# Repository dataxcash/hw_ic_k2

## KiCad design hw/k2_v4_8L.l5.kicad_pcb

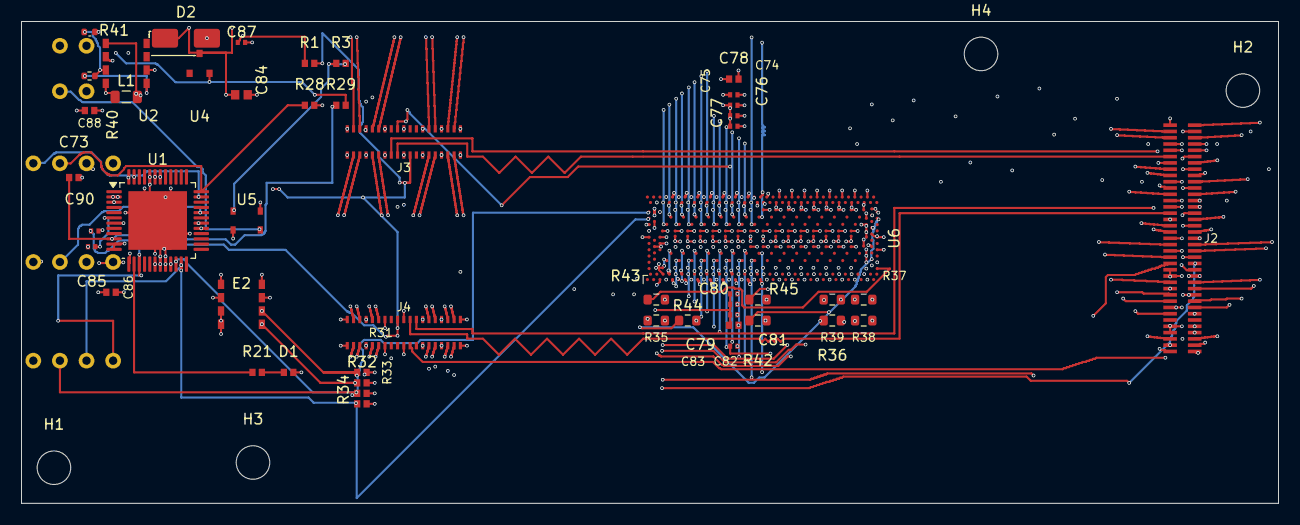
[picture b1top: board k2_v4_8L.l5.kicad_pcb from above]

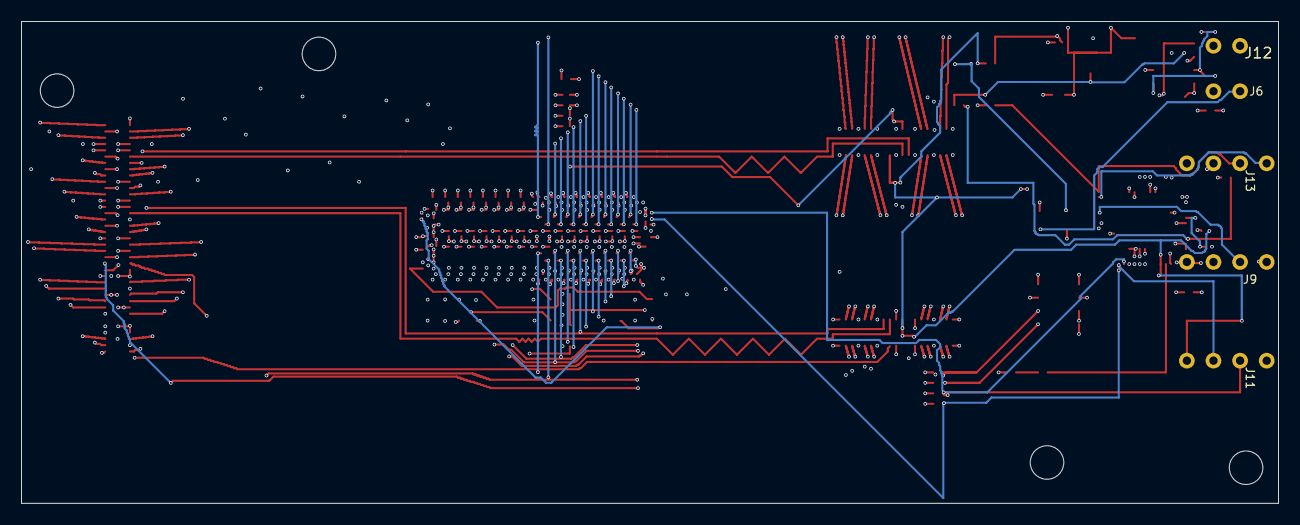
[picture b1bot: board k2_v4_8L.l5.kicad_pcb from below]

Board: 8 copper layers, 120.0 x 46.0 mm, 58 parts (5 on the bottom side), 100 nets.

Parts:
C73, C74, C75, C76, C77, C79, C80, C81, C82, C85, C87, C90: 100nF; C_0402_1005Metric
C78, C83, C88: 1uF; C_0603_1608Metric
C84: 10uF; C_0805_2012Metric
C86: 4.7uF; C_0603_1608Metric
D1: LED; LED_0603_1608Metric
D2: SS34; D_SMA
E2: FRU_EEPROM; SOIC8_FRU
H1, H2, H3, H4: MountingHole_3.2mm_M3
J2: SlimSAS_x8_SFF8654; SlimSAS_x8_SFF-8654_74pin_RASide
J3, J4: MCIO_4i_SFF1016; MCIO_4i_SFF-1016_RASide
J6: J_PWR_CTRL; PinHeader_1x02
J9: J_OOB_HEADER; PinHeader_1x04
J11: J_EC_HEADER; PinHeader_1x04
J12: J_12V_IN; PinHeader_1x02
J13: J_SWD; PinHeader_1x04
L1: 10µH; L_0805_2012Metric
R1, R28, R29: 10K; R_0603_1608Metric
R3: 220R; R_0603_1608Metric
R21, R36, R37, R39, R42, R43, R44, R45: 1K; R_0603_1608Metric
R31, R32, R33, R34: 4.7k; R_0603_1608Metric
R35: R_6K19; R_0603_1608Metric
R38: R_8K25; R_0603_1608Metric
R40: 10K; R_0402_1005Metric
R41: 5.6k; R_0402_1005Metric
U1: STM32G0B1CBT6; MCU_STM32G0_LQFP48
U2: DCDC_12V_3V3; SOIC-8_5.3x5.3mm_P1.27mm
U4: BAT54C; SOT23_BAT54C
U5: OPTO_LTV356T
U6: DS320PR1601

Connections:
12V_IN: C88.1, J12.1, L1.1, U2.4, U2.6
DS320_STRAP_A_ADDR0_7-0: R36.1, U6.B23
DS320_STRAP_A_ADDR0_15-8: R42.1, U6.FF5
DS320_STRAP_A_ADDR1_7-0: R37.1, U6.G1
DS320_STRAP_A_ADDR1_15-8: R43.1, U6.FJ3
DS320_STRAP_B_ADDR0_7-0: R38.1, U6.B25
DS320_STRAP_B_ADDR0_15-8: R44.1, U6.FJ28
DS320_STRAP_B_ADDR1_7-0: R39.1, U6.F34
DS320_STRAP_B_ADDR1_15-8: R45.1, U6.FF30
DS320_STRAP_MODE: R35.1, U6.FF24
FB_U2: R40.2, R41.1, U2.3
GND: C73.2, C74.2, C75.2, C76.2, C77.2, C78.2, C79.2, C80.2, C81.2, C82.2, C83.2, C84.2, C85.2, C86.2, C87.2, C88.2, C90.2, D1.2, E2.1, E2.3, E2.4, E2.7, J2.1, J2.4, J2.7, J2.8, J2.9, J2.10, J2.13, J2.16, J2.19, J2.22, J2.25, J2.26, J2.27, J2.28, J2.31, J2.34, J2.37, J2.38, J2.41, J2.44, J2.47, J2.49, J2.50, J2.53, J2.56, J2.59, J2.62, J2.65, J2.67, J2.68, J2.71, J2.74, J3.A1, J3.A4, J3.A7, J3.A10, J3.A13, J3.A16, J3.A19, J3.B1, J3.B4, J3.B7, J3.B10, J3.B13, J3.B16, J3.B19, J4.A1, J4.A4, J4.A7, J4.A10, J4.A13, J4.A16, J4.A19, J4.B1, J4.B4, J4.B7, J4.B10, J4.B13, J4.B16, J4.B19, J6.2, J9.3, J11.1, J12.2, J13.3, R28.2, R35.2, R36.2, R37.2, R38.2, R39.2, R41.2, R42.2, R43.2, R44.2, R45.2, U1.2, U1.3, U1.7, U1.18, U1.19, U1.20, U1.21, U1.30, U1.42, U1.43, U1.44, U1.49, U2.2, U5.2, U5.3, U6.AC4, U6.AC13, U6.AC22, U6.AC32, U6.AD2, U6.AD34, U6.AE1, U6.AE35, U6.AK4, U6.AK13, U6.AK22, U6.AK32, U6.AL2, U6.AL34, U6.AM1, U6.AM35, U6.AU4, U6.AU13, U6.AU22, U6.AU32, U6.AV2, U6.AV34, U6.AW1, U6.AW35, U6.B19, U6.BD4, U6.BD13, U6.BD22, U6.BD32, U6.BE2, U6.BE34, U6.BF1, U6.BF35, U6.BL4, U6.BL13, U6.BL22, U6.BL32, U6.BM2, U6.BM34, U6.BN1, U6.BN35, U6.BV4, U6.BV13, U6.BV22, U6.BV32, U6.BW2, U6.BW34, U6.BY1, U6.BY35, U6.CE4, U6.CE13, U6.CE22, U6.CE32, U6.CF2, U6.CF34, U6.CG1, U6.CG35, U6.CM4, U6.CM13, U6.CM22, U6.CM32, U6.CN2, U6.CN34, U6.CP1, U6.CP35, U6.CW4, U6.CW13, U6.CW22, U6.CW32, U6.CY2, U6.CY34, U6.DA1, U6.DA35, U6.DF4, U6.DF13, U6.DF22, U6.DF32, U6.DG2, U6.DG34, U6.DH1, U6.DH35, U6.DN4, U6.DN13, U6.DN22, U6.DN32, U6.DP2, U6.DP34, U6.DR1, U6.DR35, U6.DY4, U6.DY13, U6.DY22, U6.DY32, U6.E14, U6.E27, U6.E30, U6.E33, U6.EA2, U6.EA34, U6.EB1, U6.EB35, U6.EG4, U6.EG13, U6.EG22, U6.EG32, U6.EH2, U6.EH34, U6.EJ1, U6.EJ35, U6.EP4, U6.EP13, U6.EP22, U6.EP32, U6.ER2, U6.ER34, U6.ET1, U6.ET35, U6.FA15, U6.FA32, U6.FB2, U6.FB34, U6.FC3, U6.FC6, U6.FC9, U6.FC19, U6.FC23, U6.FC25, U6.FC28, U6.FD1, U6.FD35, U6.FF14, U6.FF21, U6.FF33, U6.FJ12, U6.FJ19, U6.FJ31, U6.H12, U6.H16, U6.H19, U6.H31, U6.J4, U6.J22, U6.K2, U6.K34, U6.L1, U6.L35, U6.T4, U6.T13, U6.T22, U6.T32, U6.U2, U6.U34, U6.V1, U6.V35
GPIO_LED: R21.1, U1.14
I2C1_SCL: E2.6, J2.45, R31.1, U1.47
I2C1_SDA: E2.5, J2.46, R32.1, U1.48
I2C2_SCL: J11.2, R33.1, U1.22, U6.B31
I2C2_SDA: J11.3, R34.1, U1.23, U6.B28
LED_A: D1.1, R21.2
MCU_VDD: C85.1, C86.1, E2.2, E2.8, J9.4, J13.4, R29.2, R31.2, R32.2, R33.2, R34.2, U1.6, U4.2
NRST: C73.1, R29.1, U1.10
P3V3: C74.1, C75.1, C76.1, C77.1, C78.1, C79.1, C80.1, C81.1, C82.1, C83.1, C84.1, D2.1, R40.1, U2.5, U4.3, U6.AC17, U6.AC20, U6.AK17, U6.AK20, U6.AU17, U6.AU20, U6.BD17, U6.BD20, U6.BL17, U6.BL20, U6.BV17, U6.BV20, U6.CE17, U6.CE20, U6.CM17, U6.CM20, U6.CW17, U6.CW20, U6.DF17, U6.DF20, U6.DN17, U6.DN20, U6.DY17, U6.DY20, U6.EG17, U6.EG20, U6.EP17, U6.EP20, U6.FF8, U6.FJ6, U6.T17, U6.T20
P3V3_AUX: C90.1, J3.A9, J4.A9, J11.4, R1.2, U1.15
PCIE_DN0_N: J2.40, U6.R1
PCIE_DN0_P: J2.39, U6.N2
PCIE_DN1_N: J2.43, U6.AB1
PCIE_DN1_P: J2.42, U6.Y2
PCIE_DN2_N: J2.52, U6.AG2
PCIE_DN2_P: J2.51, U6.AJ1
PCIE_DN3_N: J2.55, U6.AP2
PCIE_DN3_P: J2.54, U6.AT1
PCIE_DN4_N: J2.58, U6.BC1
PCIE_DN4_P: J2.57, U6.BA2
PCIE_DN5_N: J2.61, U6.BK1
PCIE_DN5_P: J2.60, U6.BH2
PCIE_DN6_N: J2.70, U6.BR2
PCIE_DN6_P: J2.69, U6.BU1
PCIE_DN7_N: J2.73, U6.CB2
PCIE_DN7_P: J2.72, U6.CD1
PCIE_DN_OUT0_N_MCIO: J3.A3, U6.P29
PCIE_DN_OUT0_P_MCIO: J3.A2, U6.M26
PCIE_DN_OUT1_N_MCIO: J3.A6, U6.AA29
PCIE_DN_OUT1_P_MCIO: J3.A5, U6.W26
PCIE_DN_OUT2_N_MCIO: J3.A15, U6.AH29
PCIE_DN_OUT2_P_MCIO: J3.A14, U6.AF26
PCIE_DN_OUT3_N_MCIO: J3.A18, U6.AR29
PCIE_DN_OUT3_P_MCIO: J3.A17, U6.AN26
PCIE_DN_OUT4_N_MCIO: J4.A3, U6.BB29
PCIE_DN_OUT4_P_MCIO: J4.A2, U6.AY26
PCIE_DN_OUT5_N_MCIO: J4.A6, U6.BJ29
PCIE_DN_OUT5_P_MCIO: J4.A5, U6.BG26
PCIE_DN_OUT6_N_MCIO: J4.A15, U6.BT29
PCIE_DN_OUT6_P_MCIO: J4.A14, U6.BP26
PCIE_DN_OUT7_N_MCIO: J4.A18, U6.CC29
PCIE_DN_OUT7_P_MCIO: J4.A17, U6.CA26
PCIE_REFCLK0_N: J2.12, J3.A12
PCIE_REFCLK0_P: J2.11, J3.A11
PCIE_REFCLK1_N: J2.30, J4.A12
PCIE_REFCLK1_P: J2.29, J4.A11
PCIE_UP0_N: J3.B3, U6.N34
PCIE_UP0_P: J3.B2, U6.R35
PCIE_UP1_N: J3.B6, U6.Y34
PCIE_UP1_P: J3.B5, U6.AB35
PCIE_UP2_N: J3.B15, U6.AJ35
PCIE_UP2_P: J3.B14, U6.AG34
PCIE_UP3_N: J3.B18, U6.AT35
PCIE_UP3_P: J3.B17, U6.AP34
PCIE_UP4_N: J4.B3, U6.BA34
PCIE_UP4_P: J4.B2, U6.BC35
PCIE_UP5_N: J4.B6, U6.BH34
PCIE_UP5_P: J4.B5, U6.BK35
PCIE_UP6_N: J4.B15, U6.BU35
PCIE_UP6_P: J4.B14, U6.BR34
PCIE_UP7_N: J4.B18, U6.CD35
PCIE_UP7_P: J4.B17, U6.CB34
PCIE_UP_OUT0_N_J2: J2.3, U6.M7
PCIE_UP_OUT0_P_J2: J2.2, U6.P10
PCIE_UP_OUT1_N_J2: J2.6, U6.W7
PCIE_UP_OUT1_P_J2: J2.5, U6.AA10
PCIE_UP_OUT2_N_J2: J2.15, U6.AF7
PCIE_UP_OUT2_P_J2: J2.14, U6.AH10
PCIE_UP_OUT3_N_J2: J2.18, U6.AN7
PCIE_UP_OUT3_P_J2: J2.17, U6.AR10
PCIE_UP_OUT4_N_J2: J2.21, U6.AY7
PCIE_UP_OUT4_P_J2: J2.20, U6.BB10
PCIE_UP_OUT5_N_J2: J2.24, U6.BG7
PCIE_UP_OUT5_P_J2: J2.23, U6.BJ10
PCIE_UP_OUT6_N_J2: J2.33, U6.BP7
PCIE_UP_OUT6_P_J2: J2.32, U6.BT10
PCIE_UP_OUT7_N_J2: J2.36, U6.CA7
PCIE_UP_OUT7_P_J2: J2.35, U6.CC10
PERSTA#: C87.1, J2.48, J3.B11, R1.1, U1.11, U1.12
PERSTB#: J2.66, J4.B11
PWR_BTN_ISO: R3.2, U5.1
PWR_BTN_OUT: R3.1, U1.13
PWR_CTRL_OUT: J6.1, U5.4
SWCLK_BOOT0: J13.2, R28.1, U1.36
SWDIO: J13.1, U1.35
SW_U2: D2.2, L1.2, U2.1
UART_RX: J9.2, U1.32
UART_TX: J9.1, U1.29
